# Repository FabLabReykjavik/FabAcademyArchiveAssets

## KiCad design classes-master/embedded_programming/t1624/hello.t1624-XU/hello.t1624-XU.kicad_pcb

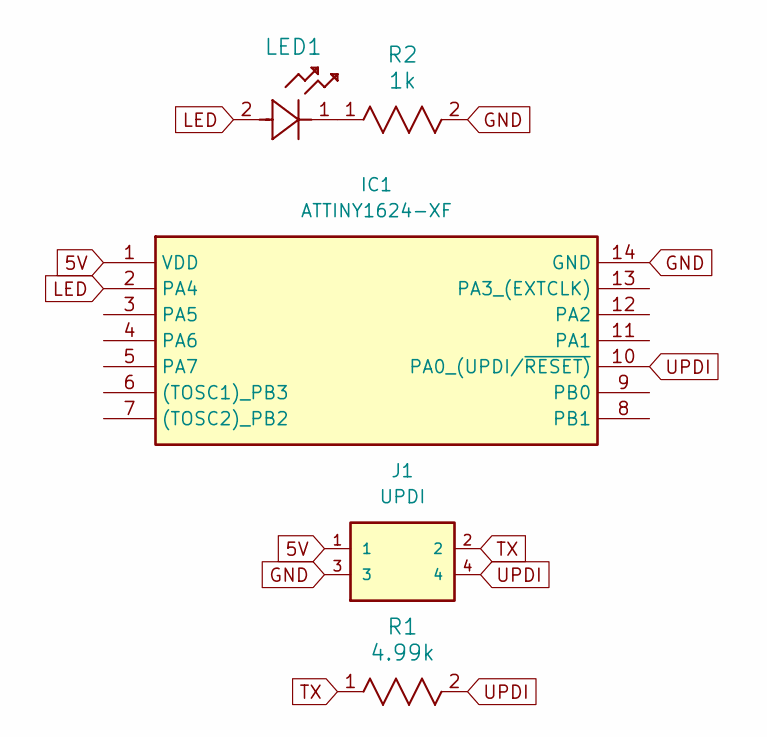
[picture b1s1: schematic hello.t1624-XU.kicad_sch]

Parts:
IC1: ATTINY1624-XF; TSSOP 14; Manufacturer_Part_Number ATTINY1624-XF; Mouser Part Number 556-ATTINY1624-XF
J1: UPDI; 2x2x0.5 header
LED1: B1911USD-20D000114U1930; LED 0603
R1: 4.99k; Resistor 0603
R2: 1k; Resistor 0603

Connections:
5V: IC1.1 (VDD), J1.1
GND: IC1.14 (GND), J1.3, R2.2
LED: IC1.2 (PA4), LED1.2
unnamed: LED1.1, R2.1
TX: J1.2, R1.1
UPDI: IC1.10 (PA0_(UPDI/~RESET)), J1.4, R1.2

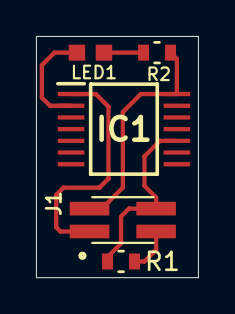
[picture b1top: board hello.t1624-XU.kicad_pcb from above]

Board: 2 copper layers, 9.0 x 13.4 mm, 5 parts (0 on the bottom side), 6 nets.

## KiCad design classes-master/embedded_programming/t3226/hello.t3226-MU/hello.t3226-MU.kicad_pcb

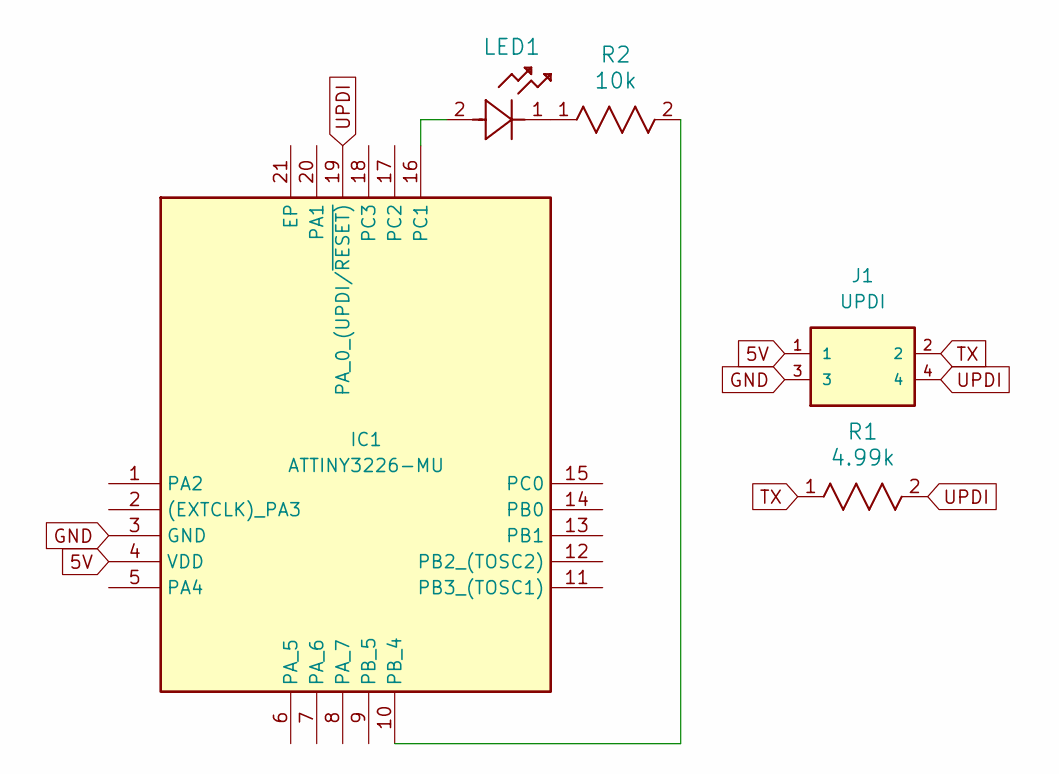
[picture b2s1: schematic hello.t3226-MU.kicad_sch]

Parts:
IC1: ATTINY3226-MU; ATtiny3226-MU; Manufacturer_Part_Number ATTINY3226-MU; Mouser Part Number 579-ATTINY3226-MU
J1: UPDI; 2x2x0.5 header
LED1: B1911USD-20D000114U1930; LED 0603
R1: 4.99k; Resistor 0603
R2: 10k; Resistor 0603

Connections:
5V: IC1.4 (VDD), J1.1
GND: IC1.3 (GND), J1.3
unnamed: IC1.10 (PB_4), R2.2
unnamed: IC1.16 (PC1), LED1.2
unnamed: LED1.1, R2.1
TX: J1.2, R1.1
UPDI: IC1.19 (PA_0_(UPDI/~RESET)), J1.4, R1.2

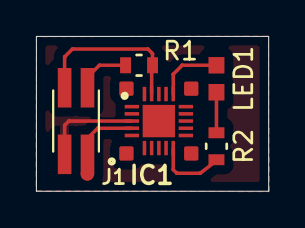
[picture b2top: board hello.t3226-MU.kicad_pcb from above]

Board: 2 copper layers, 12.9 x 8.6 mm, 5 parts (0 on the bottom side), 7 nets.

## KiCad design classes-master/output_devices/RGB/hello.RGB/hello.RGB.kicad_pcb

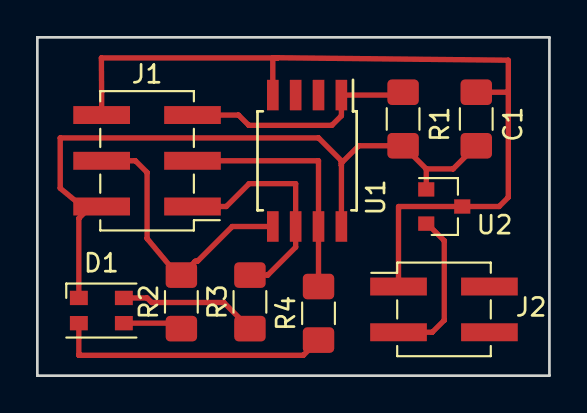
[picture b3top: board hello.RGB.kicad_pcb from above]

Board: 2 copper layers, 28.4 x 18.8 mm, 10 parts (0 on the bottom side), 10 nets.

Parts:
C1: 1uF; C_1206_3216Metric_Pad1.42x1.75mm_HandSolder
D1: CLV1L-FKB; LED_Cree-PLCC4_3.2x2.8mm_CCW
J1: AVR-ISP-6; PinHeader_2x03_P2.54mm_Vertical_SMD
J2: Power; PinHeader_2x02_P2.54mm_Vertical_SMD
R1: 10K; R_1206_3216Metric_Pad1.42x1.75mm_HandSolder
R2, R4: 1k; R_1206_3216Metric_Pad1.42x1.75mm_HandSolder
R3: 499; R_1206_3216Metric_Pad1.42x1.75mm_HandSolder
U1: ATtiny45V-10SU; SOIJ-8_5.3x5.3mm_P1.27mm
U2: LM3480-5.0; SOT-23

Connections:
unnamed: C1.1, D1.1, J1.2, R1.1, U1.8, U2.1
unnamed: C1.2, J1.6, J2.1, U1.4, U2.3
unnamed: D1.2, R4.1
unnamed: D1.3, R2.1
unnamed: D1.4, R3.1
unnamed: J1.1, R3.2, U1.6
unnamed: J1.3, R4.2, U1.7
unnamed: J1.4, R2.2, U1.5
unnamed: J1.5, R1.2, U1.1
unnamed: J2.3, U2.2
